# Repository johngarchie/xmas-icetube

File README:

##########################
## XMAS-ICETUBE PROJECT ##
##########################

Several years ago, my father gave me an Adafruit Ice Tube Clock kit as
a Christmas gift.  As an excuse to learn AVR programming, I started
playing with the firmware.  Eventually, none of the original Adafruit
code remained, and the result was a feature-rich reimplementation of
the Adafruit firmware.

Once the firmware was mature, I decided to revise the hardware design
to support many of the hacks and mods described on the Adafruit
forums.  With the help of other clock hackers, especially Phil DeGruy
and Russell Walker, the xmas-icetube hardware revision became a reality.

Today, the xmas-icetube firmware still runs on the Adafruit Ice Tube
Clock v1.1 as well as the xmas-icetube hardware revision.  For more
information on the firmware and hardware portions of this project,
please check out the firmware/README and hardware/README files.

Finally, although the xmas-icetube project is named after Christmas,
it is designed for use year-round.  The name is also a reference to
Christmas as a cultural holiday--not a religious one.  I sincerely
hope this project is compatible with all religions.

  John Archie <www.jarchie.com/email>
  April 2, 2014

###################
## USER FEEDBACK ##
###################

Below is a selection of comments posted on the Adafruit Clocks
forum.  They are listed in reverse chronological order.  And to
everyone quoted below:  Thank you all for the kind words!

  "[The xmas firmware] just worked from the beginning...
   Great documentation!"
     --MikeHg
       http://forums.adafruit.com/viewtopic.php?p=324261#p324261

  "Every mod works beautifully...  The code truly is clever...
   [John's] code is so clean that it's easy to add things."
     --rcb
       http://forums.adafruit.com/viewtopic.php?p=244224#p244224

  "This firmware is really cool. I highly recommend anyone with an
   ATmega328p lying around to program it with this firmware and use
   it instead of the one that comes with the kit."
     --motocoder
       http://forums.adafruit.com/viewtopic.php?p=243916#p243916

  "[John] has done a lot of nice work and added a lot of features.
   I can recommend his firmware as an upgrade..."
     --adafruit_support_bill,
       http://forums.adafruit.com/viewtopic.php?p=211476#p211476

  "...I LOVE your firmware, and for about 2 weeks I was still
   finding new options and features in the menu."
     --wildtang3nt
       http://forums.adafruit.com/viewtopic.php?p=204665#p204665

  "+10 for John's firmware!  Please do not let the 'xmas' name sway
   you from giving it a try. It's the most feature complete Ice-Tube
   Clock firmware to date."
     --revnull
       http://forums.adafruit.com/viewtopic.php?p=180609#p180609

##############
## FEATURES ##
##############

The xmas-icetube firmware offers the following improvements over
the official Adafruit firmware:

  - GPS synchronized timekeeping*
  - fully automatic compensation for clock drift
  - animated display transitions
  - multiple time and date formats
  - DST support (USA, EU, or manual)
  - pulsing display brightness during alarm and snooze
  - three alarm times for selectable days of the week
  - functional alarm during power outage**
  - finely adjustable alarm volume (from 0 to 10)
  - progressive alarm option (gradually increasing volume)
  - adjustable snooze duration
  - selectable alarm sound (high frequency beeps, low frequency beeps,
    high frequency three beep pulse, low frequency three beep pulse,
    Merry Christmas, Big Ben, Reveille, or For He's a Jolly Good Fellow)
  - 4-fold improvement in battery life
  - no beeping or time loss after external power failure
  - low battery warning before battery failure
  - per-digit brightness adjustment for uneven displays
  - larger range for user-configured display brightness
  - optionally disable display during specified time periods

*  An external GPS module, such as the Adafruit Ultimate GPS, is
   necessary to support GPS synchronized timekeeping.

** Without external power, the alarm sounds with loud high frequency
   beeps.  The only way to turn the alarm on or off is with the alarm
   switch.  Snooze is not supported.

The following additional features are supported on the xmas-icetube
hardware revision, but the Adafruit Ice Tube Clock v1.1 can be
modified to support any or all of the following as well:

  - automatic brightness control by ambient light
  - optionally disable display at night (when dark)
  - 25-fold improvement in battery life
  - highly accurate temperature compensated timekeeping
  - IV-18 tube driven to specifications (providing more even
    display illumination and preventing cathode poisoning)

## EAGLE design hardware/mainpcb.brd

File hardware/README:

####################################
## XMAS-ICETUBE HARDWARE REVISION ##
####################################

The xmas-icetube hardware revision is a revision of the Adafruit Ice Tube
Clock v1.1 hardware design to support many of the hacks and mods that have
been posted to the Adafruit forums over the years.  The original circuit
board has been extensively revised, but the case and overall look of the
clock is nearly identical to the original design.

The xmas-icetube hardware revision is discussed in the following thread:

    http://forums.adafruit.com/viewtopic.php?t=43836

##############
## FEATURES ##
##############

The xmas-icetube revision has the following improvements over the original
Adafruit design.  Although all of these features are incorporated into the
xmas-icetube board, many of the links given are oriented toward modifying
the original Adafruit clock to include the corresponding features.  Those
discussions are still relevant to the xmas-icetube revision, however.

* IV-18 tube driven to specifications:  The Adafruit design runs the IV-18
  in a way that results in inconsistent illumination across the display,
  and on some tubes, the effect is quite noticeable.  The original IV-18
  drive also accelerated the process of cathode poisoning.  Driving the
  IV-18 as the designers intended ensures uniform illumination and makes
  the tube less prone to cathode poisoning.

  http://forums.adafruit.com/viewtopic.php?t=23586
  http://forums.adafruit.com/viewtopic.php?t=41811

* Automatic dimming:  A photoresistor allows automatic dimming as
  appropriate for the ambient lighting.  The Adafruit design does,
  however, have an expansion area that can also be used to this end.

  http://forums.adafruit.com/viewtopic.php?t=12932

* 25-fold reduction in sleep current:  Unless the clock is without power
  for over a year, the battery should never need replacement.

  http://forums.adafruit.com/viewtopic.php?t=36697  
  http://forums.adafruit.com/viewtopic.php?p=219736#p219736

* Temperature compensated timekeeping:  A DS18B20 temperature sensor next
  to the clock crystal allows the software to compensate for temperature-
  related timekeeping error.  When combined with software-based drift
  correction, the resulting accuracy should be comparable to a temperature
  compensated quartz oscillator.

  http://forums.adafruit.com/viewtopic.php?t=43998
  http://forums.adafruit.com/viewtopic.php?f=41&t=12720

* GPS solder points:  Through-hole solder points allow easier installation
  of an external GPS unit for time synchronization.

  http://forums.adafruit.com/viewtopic.php?t=36873
  http://learn.adafruit.com/ice-tube-clock-kit/mods

  Alternatively, these solder points may also be used for installing a
  dedicated temperature compensated crystal oscillator instead of the
  DS18B20 temperature sensor above.

  http://forums.adafruit.com/viewtopic.php?&t=14941

* Robust in-system programming:  The clock may be programmed regardless of
  whether the display and side board are installed.  I recommend powering
  the clock with external power during programming, but a programming
  jumper provides a way to force the clock into sleep mode to ensure minimal
  power consumption if powered by the programmer instead.  I recommend
  using the jumper if using the AVR Dragon programmer, as the Dragon can
  barely provide enough power for programming alone.  But the jumper is
  unnecessary for most programmers including the Adafruit USBtinyISP.

  http://forums.adafruit.com/viewtopic.php?t=41975

* Robust microcontroller environment:  The microcontroller now has a
  decoupling capacitor and 10K pull-up on the reset pin.  These
  components make the clock less sensitive to electrical noise and
  ensure reliable operation.

Finally, although the xmas-icetube firmware is compatible with *both* the
original Adafruit clock and the xmas-icetube hardware revision, the
xmas-icetube revision is not compatible with firmwares developed
specifically for the Adafruit clock.

##########################
## COLLECTING THE PARTS ##
##########################

The current versions of the xmas-icetube custom parts are:

  - main board   (Rev. D)
  - side board   (Rev. C)
  - acrylic case (Rev. A)

I ordered my circuit boards from OSH Park and have shared those uploads
in case others would like to do the same:

    http://www.oshpark.com/shared_projects/6xAVpeHb
    http://www.oshpark.com/shared_projects/PiRXWH3F

I ordered the 3mm clear acrylic parts from Ponoko and have also shared
that design:

    http://www.ponoko.com/showroom/jarchie

For those in Europe, Formulor (http://www.formulor.de/) is an alternative
source for the acrylic parts.  Formulor is a Ponoko partner and accepts
the same SVG design format.  Many thanks to Tobias Scharmann for
suggesting this service.

See the enclosed bill of materials (BOM.csv) for a complete parts list,
including manufacturers, suppliers, and part numbers.

########################
## BUILDING THE CLOCK ##
########################

For aesthetic reasons, the xmas-icetube design uses TO-92 packages for the
voltage regulators, so their ability to burn off excess voltage is limited.
The 9VDC input should stay below 10v at 120 mA to be on the safe side:  A
standard regulated switching-type 9v adapter should work fine, but I
recommend against using an older, unregulated, transformer-type wall wort.

Alternatively, the board will accommodate regulators in TO-220 packages,
even though the silkscreen shows TO-92 packages.  The holes are a bit small
for TO-220s, so it might be necessary to file down the TO-220 leads to make
them narrower, but those packages will work with a bit of extra effort.
Although, I do prefer the TO-92s, TO-220s would look okay--just a bit bulky.

When assembling the parts, I suggest building the circuit incrementally and
testing each section after it is built.  See the Eagle schematics for the
parts in each section.

1.  Solder the "5V Power Supply" parts.  Connect the 9v adaptor and verify
    that the power supply outputs 5v; disconnect and proceed.

2.  Solder the "Temperature Sensor" parts.  (It's easier to solder R9
    before inserting the microcontroller into its socket.)

3.  Solder the "Microcontroller", "ISP Header", "Battery Sensor", and
    "Speaker" parts.  Program the ATmega328P (see the firmware/README file
    for details).  When powered with the AC adaptor, the speaker should
    beep when powered for the first time.  Keep the AC adaptor connected
    for at least ten seconds after hearing the beep.

    If the speaker does not beep, ensure the programming jumper has been
    removed and that the ATmega328P is properly programmed.  If the speaker
    beeps repeatedly at 8 second intervals, the problem is most likely with
    the crystal oscillator.  If the oscillator parts and connections are
    good, cleaning excess rosin from the board with a toothbrush and
    rubbing alcohol might fix the problem, but make sure the board is
    completely dry before powering it again.

4.  Solder the "5VAC Cathode/Filament Supply" parts.  Measure the AC voltage
    between the two push-pull outputs (AC1 and AC2).  The push-pulls should
    provide high frequency, square wave, alternating current, which most
    multimeters cannot measure accurately.  Without a load, the LM317 will not
    effectively regulate voltage anyway, so multimeter accuracy does not
    matter.  So ensure that AC1 and AC2 are providing alternating current,
    but the amount of voltage measured is not important.

5.  Solder the "Tube 30-60VDC Boost Supply" parts.  Note that the joined
    leads of Q2 should be oriented toward C6.  Connect the 9v adaptor and
    verify that the boost circuit indeed provides 50-60 volts.

6.  Solder the "VFD Anode/Segment Controller" and "VFD Tube / Side PCB"
    parts.  Attach the side board to the main board, connect the 9v
    adaptor, and verify that the VFD display is functional.

7.  Solder the "Buttons and Alarm Switch" parts.  Connect the 9v adaptor
    and verify that the buttons and alarm switch function properly.

8.  Solder the "Battery Backup" parts and insert a battery, but before
    soldiering the battery case, apply a small amount of solder to the
    battery's ground connection (large square pad).  A small amount of
    solder will add height to the square pad connection and ensure a good
    connection between the battery and ground.

    Connect the 9v adaptor, set the time, disconnect the 9v adaptor for ten
    minutes, connect it again, and verify that the clock kept the correct
    time.  Because the clock is extremely power-efficient during sleep, the
    capacitors store enough charge to keep the clock running for 3-5
    minutes.  Leaving the clock unplugged for ten minutes ensures that the
    backup battery is actually in use.

9.  Solder the "Light Sensor" parts.  So the clock can accurately gauge
    ambient lighting, install the photoresistor such that it points towards
    the front of the clock and away from the tube.  Connect the 9v adaptor,
    and using a flashlight, lamp, or similar, verify that the clock
    responds to changes in ambient light.

10. Assemble the acrylic case and enjoy!

##############################
## EDITING THE DESIGN FILES ##
##############################

The board revisions can be opened and and modified with Eagle,
which is available from CadSoft:

    http://www.cadsoftusa.com/

The case revision may be viewed and modified in Inkscape:

    http://inkscape.org/

######################
## ACKNOWLEDGEMENTS ##
######################

The Adafruit Ice Tube Clock board was loosely based on the inGrid
IV-18 clock by Riad S. Wahby.  My xmas-icetube board revision is based
on the Adafruit Ice Tube Clock board by Lady Ada.

The clock case was originally designed by Amanda Wozniak (w0z), and I have
only made minor adjustments to her design.  Adafruit forum user Daygecko
also deserves credit for finding clear machine nuts and bolts from
McMaster-Carr, which give the assembled case a cleaner look.

Phil DeGruy (PhilD13) reviewed my initial design and suggested several
components; the ZVN2110A and ZVP2001A MOSFETs in particular were
especially useful for generating AC for the IV-18 filament.  Phil
also found many alternative parts for the bill of materials which cost
less than my original selections.

I also had fruitful discussions with both Phil DeGruy and Russell Walker
(Russell27), mostly  in regard to properly driving the IV-18 tube.  Phil
and Russell built their own xmas-icetube clocks and provided useful
feedback on the overall design.

Because I am inexperienced in electronics design, I must add the following
disclaimer:  Those cited in this section cannot be faulted for any bugs in
the xmas-icetube hardware revision.

#############
## LICENSE ##
#############

The xmas-icetube hardware revision may be used under the Attribution-
ShareAlike 3.0 (CC BY-SA 3.0), available from Creative Commons:

    http://creativecommons.org/licenses/by-sa/3.0/

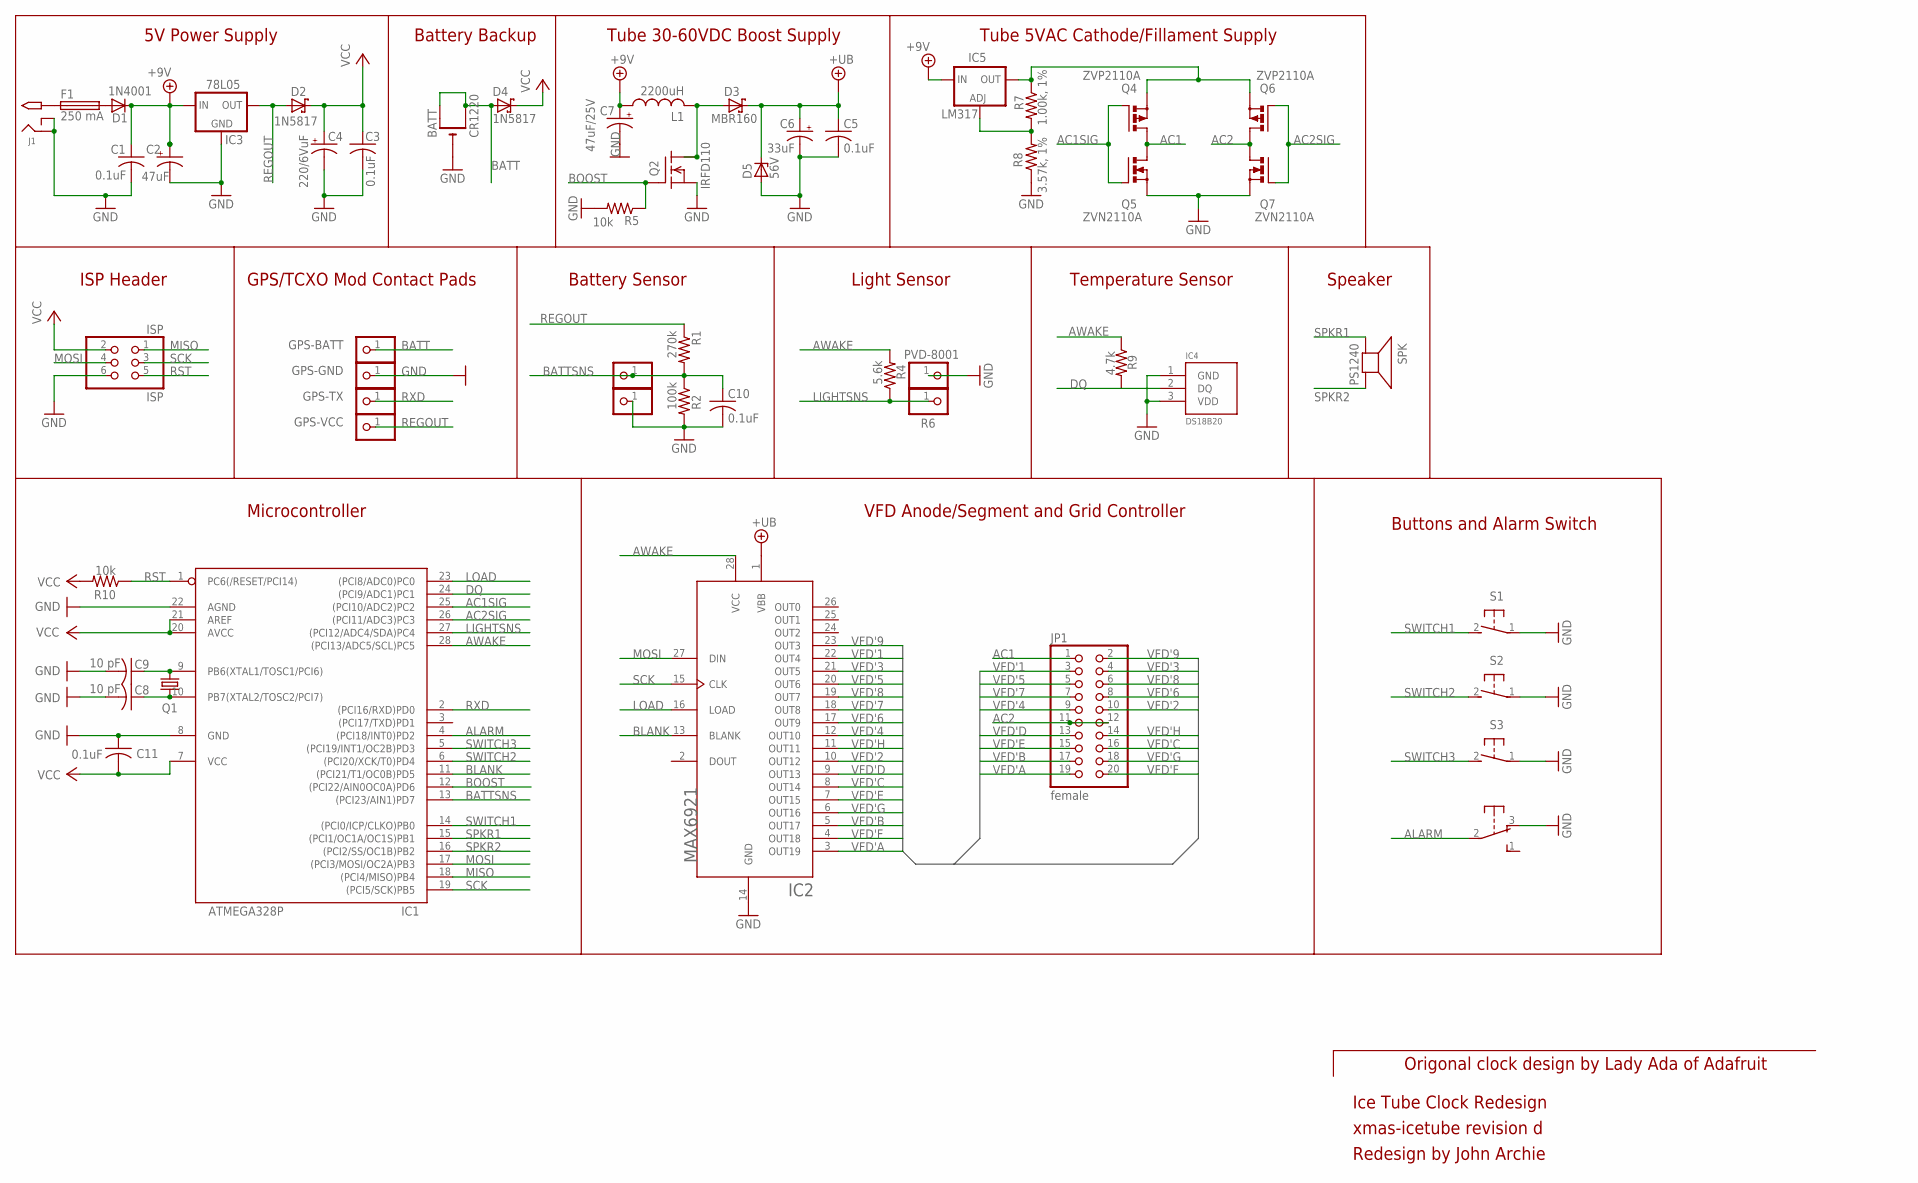
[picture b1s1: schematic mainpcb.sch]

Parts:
BATT: CR1220; CR1220-THM
C1, C3, C11: 0.1uF; C025-025X050
C2: 47uF; E2,5-6
C4: 220/6VuF; E2,5-6
C5, C10: 0.1uF; C025-024X044
C6: 33uF; E3,5-8
C7: 47uF/25V; E2,5-6
C8, C9: 10 pF; C025-024X044
CT2, CT3: PINHD-1X1; 1X01
D1: 1N4001; DO41-10
D2, D4: 1N5817; DO41-10
D3: MBR160; DO41-10
D5: 56V; DO41Z10
F1: 250 mA; TE5
GPS-BATT: PINHD-1X1; 1X01
GPS-GND: PINHD-1X1; 1X01
GPS-TX: PINHD-1X1; 1X01
GPS-VCC: PINHD-1X1; 1X01
IC1: ATMEGA328P; DIL28/3
IC2: MAX6921; PLCC-S28
IC3: 78L05; TO92-LINE
IC4: DS18B20; TO92
IC5: LM317; TO92-LINE
ISP: ISP; 2X03
J1: 2.1MMJACK; PJ-102A
JP1: female; 2X10
L1: 2200uH; 6000
Q1: 32.768 khz; TC26V
Q2: IRFD110; DIL04
Q4, Q6: ZVP2110A; TO92-FLAT
Q5, Q7: ZVN2110A; TO92-FLAT
R1: 270k; 0207/10
R2: 100k; 0207/10
R4: 5.6k; 0207/5V
R5, R10: 10k; 0207/5V
R6: PVD-8001; 1X01
R6.1: PINHD-1X1; 1X01
R7: 1.00k, 1%; 0207/5V
R8: 3.57k, 1%; 0207/5V
R9: 4.7k; 0207/10
S1, S2, S3: 31-XX; B3F-31XX
SPK: PS1240; PS12
SW1: OS102011MA1Q

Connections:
+9V: C1.1, C2.+, C7.+, D1.C, IC3.3 (IN), IC5.3 (IN), L1.1
+UB: C5.1, C6.+, D3.C, D5.C, IC2.1 (VBB)
AC1: JP1.1, Q4.3 (D), Q5.3 (D)
AC1SIG: IC1.25 ((PCI10/ADC2)PC2), Q4.2 (G), Q5.2 (G)
AC2: JP1.11, JP1.12, Q6.3 (D), Q7.3 (D)
AC2SIG: IC1.26 ((PCI11/ADC3)PC3), Q6.2 (G), Q7.2 (G)
ALARM: IC1.4 ((PCI18/INT0)PD2), SW1.2
AWAKE: IC1.28 ((PCI13/ADC5/SCL)PC5), IC2.28 (VCC), R4.2, R9.1
BATT: BATT.+1 (+), BATT.+2 (+1), D4.A, GPS-BATT.1
BATTSNS: C10.1, CT2.1, IC1.13 ((PCI23/AIN1)PD7), R1.2, R2.1
BLANK: IC1.11 ((PCI21/T1/OC0B)PD5), IC2.13 (BLANK)
BOOST: IC1.12 ((PCI22/AIN0OC0A)PD6), Q2.3 (G), R5.1
DQ: IC1.24 ((PCI9/ADC1)PC1), IC4.2 (DQ), R9.2
GND: BATT.-, C1.2, C2.-, C3.2, C4.-, C5.2, C6.-, C7.-, C8.2, C9.2, C10.2, C11.1, CT3.1, D5.A, GPS-GND.1, IC1.8 (GND), IC1.22 (AGND), IC2.14 (GND), IC3.2 (GND), IC4.1 (GND), IC4.3 (VDD), ISP.6, J1.RING, J1.RING_SW, Q2.4 (S), Q5.1 (S), Q7.1 (S), R2.2, R5.2, R6.1, R8.1, S1.1, S2.1, S3.1, SW1.3 (O)
LIGHTSNS: IC1.27 ((PCI12/ADC4/SDA)PC4), R4.1, R6.1.1
LOAD: IC1.23 ((PCI8/ADC0)PC0), IC2.16 (LOAD)
MISO: IC1.18 ((PCI4/MISO)PB4), ISP.1
MOSI: IC1.17 ((PCI3/MOSI/OC2A)PB3), IC2.27 (DIN), ISP.4
unnamed: C9.1, IC1.9 (PB6(XTAL1/TOSC1/PCI6)), Q1.2
unnamed: D3.A, L1.2, Q2.1 (D), Q2.2 (D1)
unnamed: C8.1, IC1.10 (PB7(XTAL2/TOSC2/PCI7)), Q1.1
unnamed: F1.1, J1.TIP
unnamed: D1.A, F1.2
unnamed: IC5.1 (ADJ), R7.2, R8.2
unnamed: IC5.2 (OUT), Q4.1 (S), Q6.1 (S), R7.1
REGOUT: D2.A, GPS-VCC.1, IC3.1 (OUT), R1.1
RST: IC1.1 (PC6(/RESET/PCI14)), ISP.5, R10.1
RXD: GPS-TX.1, IC1.2 ((PCI16/RXD)PD0)
SCK: IC1.19 ((PCI5/SCK)PB5), IC2.15 (CLK), ISP.3
SPKR1: IC1.15 ((PCI1/OC1A/OC1S)PB1), SPK.P$1 (+)
SPKR2: IC1.16 ((PCI2/SS/OC1B)PB2), SPK.P$2 (-)
SWITCH1: IC1.14 ((PCI0/ICP/CLKO)PB0), S1.2 (S)
SWITCH2: IC1.6 ((PCI20/XCK/T0)PD4), S2.2 (S)
SWITCH3: IC1.5 ((PCI19/INT1/OC2B)PD3), S3.2 (S)
VCC: C3.1, C4.+, C11.2, D2.C, D4.C, IC1.7 (VCC), IC1.20 (AVCC), IC1.21 (AREF), ISP.2, R10.2
VFD'1: IC2.22 (OUT4), JP1.3
VFD'2: IC2.10 (OUT12), JP1.10
VFD'3: IC2.21 (OUT5), JP1.4
VFD'4: IC2.12 (OUT10), JP1.9
VFD'5: IC2.20 (OUT6), JP1.5
VFD'6: IC2.17 (OUT9), JP1.8
VFD'7: IC2.18 (OUT8), JP1.7
VFD'8: IC2.19 (OUT7), JP1.6
VFD'9: IC2.23 (OUT3), JP1.2
VFD'A: IC2.3 (OUT19), JP1.19
VFD'B: IC2.5 (OUT17), JP1.17
VFD'C: IC2.8 (OUT14), JP1.16
VFD'D: IC2.9 (OUT13), JP1.13
VFD'E: IC2.7 (OUT15), JP1.15
VFD'F: IC2.4 (OUT18), JP1.20
VFD'G: IC2.6 (OUT16), JP1.18
VFD'H: IC2.11 (OUT11), JP1.14

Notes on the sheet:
5V Power Supply
GPS/TCXO Mod Contact Pads
Tube 30-60VDC Boost Supply
Ice Tube Clock Redesign
xmas-icetube revision d
Redesign by John Archie
Tube 5VAC Cathode/Fillament Supply
ISP Header
Battery Backup
Microcontroller
VFD Anode/Segment and Grid Controller
Buttons and Alarm Switch
Battery Sensor
Light Sensor
Temperature Sensor
Speaker
Origonal clock design by Lady Ada of Adafruit

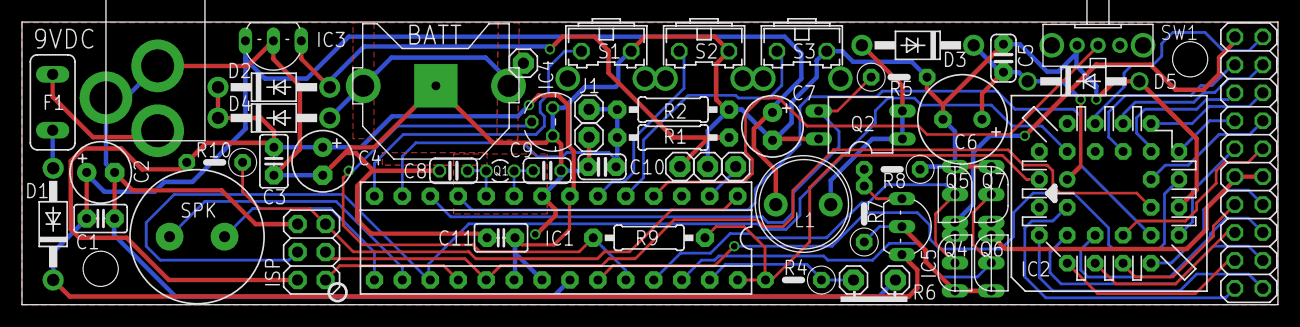
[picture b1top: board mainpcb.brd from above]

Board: 2 copper layers, 114.2 x 25.7 mm, 54 parts (0 on the bottom side), 52 nets.

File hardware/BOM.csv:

"Name","Description","Manufacturer","Manufacturer Part","Supplier","Supplier Part"
"main board","xmas-icetube main board (rev. d)","OSH Park",,"OSH Park",
"side board","xmas-icetube side board (rev. c) ","OSH Park",,"OSH Park",
"acrylic case","xmas-icetube acrylic case (rev. a)","Ponoko",,"Ponoko",
"nuts (10x)","4-40 polycarbonate hex nut","McMaster-Carr","94905A005","McMaster-Carr","94905A005"
"bolts (8x)","4-40 polycarbonate phillips screw","McMaster-Carr","93140A109","McMaster-Carr","93140A109"
"9VAC","9 v adaptor, 2.1mm jack (International)","CUI Inc","EMSA090067-P5P-SZ","Digi-Key","T1085-P5P-ND"
"9VAC (alt)","9 volt adaptor, 2.1mm jack (North America)","Volgen America/Kaga Electronics USA","KTPS05-09006U","Digi-Key","62-1167-ND"
"BATT","coin cell","Energizer","CR1220","Amazon","B003CU3E2Q"
"display","antique vacuum florescent display ","Russia (discontinued, NOS)","IV-18","eBay/Adafruit","IV-18"
"9VAC'","2.1mm power jack","CUI Inc","PJ-202A","Digi-Key","CP-202A-ND"
"BATT'","coin cell holder","Keystone Electronics",3001,"Digi-Key","3001K-ND"
"C1,C3,C10,C11","0.1uF 50v cap","TDK Corporation","FK18X7R1H104K","Digi-Key","445-5303-ND"
"C2,C7","47uF 35v cap","Panasonic Electronic Components","ECA-1VHG470","Digi-Key","P5550-ND"
"C4","220uF 6.3v cap","Panasonic Electronic Components","ECA-0JHG221","Digi-Key","P5506-ND"
"C5","0.1uF 100v cap","AVX Corporation","SR201C104KAR","Digi-Key","478-4855-ND"
"C6","33uF 100v cap","Panasonic Electronic Components","EEU-FC2A330L","Digi-Key","P10772-ND"
"C8,C9","10pF 50v cap","Vishay BC Components","K100J15C0GF5TL2","Digi-Key","BC1001CT-ND"
"D1","50v 1A general purpose diode","Fairchild Semiconductor","1N4001","Digi-Key","1N4001FSCT-ND"
"D2,D4","20v 1A Schottky diode","Fairchild Semiconductor","1N5817","Digi-Key","1N5817FSCT-ND"
"D3","60v 1A Schottky diode","ON Semiconductor","MBR160G","Digi-Key","MBR160GOS-ND"
"D5","56v 1.3W Zener diode","Vishay Semiconductor Diodes Division","1N4758A-TR","Digi-Key","1N4758AVSCT-ND"
"F1","250 mA resettable fuse","TE Connectivity","RXEF025-2","Digi-Key","RXEF025CT-ND"
"IC1","Microcontroller","Atmel","ATMEGA328P-PU","Digi-Key","ATMEGA328P-PU-ND "
"IC1'","28 pin DIP socket","3M","4828-3004-CP","Digi-Key","3M5480-ND"
"IC2","VFD grid/segment driver","Maxim Integrated","MAX6921AQI+","Digi-Key","MAX6921AQI+-ND"
"IC2'","28 pin PLCC socket","Assmann WSW Components","A-CCS28-Z-R","Digi-Key","AE10055-ND"
"IC3","5v voltage regulator","ON Semiconductor","MC78L05ABPG","Digi-Key","MC78L05ABPGOS-ND"
"IC4","temperature sensor","Maxim Integrated","DS18B20+","Mouser","700-DS18B20+"
"IC5","LM317 voltage regulator","ON Semiconductor","LM317LZG","Digi-Key","LM317LZGOS-ND"
"ISP","2x3 0.1inx0.1in ISP header","3M","961206-6404-AR","Digi-Key","3M9459-ND"
"J1","standard jumper","Sullins Connector Solutions","QPC02SXGN-RC","Digi-Key","S9337-ND"
"J1 (alt)","jumper with handle (alternative)","Sullins Connector Solutions","NPC02SXON-RC","Digi-Key","S9341-ND"
"J1'","1x2 0.1in male header","FCI","77311-118-02LF","Digi-Key","609-4434-ND"
"JP1","2x10 0.1inx0x.1in female header","Sullins Connector Solutions","PPPC102LFBN-RC","Digi-Key","S6106-ND"
"JP2","2x10 0.1inx0x.1in male right angle header","FCI","68021-120HLF","Digi-Key","609-3338-ND"
"L1","2.2mH 0.24A inductor","Murata Power Solutions Inc","13R225C","Digi-Key","811-2054-ND"
"Q1","clock crystal oscillator","ABRACON","AB38T-32.768KHZ","Mouser","815-AB38T-32.768KHZ"
"Q2","100v N-channel MOSFET","Vishay Siliconix","IRFD110PBF","Digi-Key","IRFD110PBF-ND"
"Q3","removed from design",,,,
"Q4,Q6","100v P-channel MOSFET","Diodes Inc","ZVP2110A","Digi-Key","ZVP2110A-ND"
"Q5,Q7","100v N-channel MOSFET","Diodes Inc","ZVN2110A","Digi-Key","ZVN2110A-ND"
"R1","270k 5% resistor","Yageo","CFR-25JB-52-270K","Digi-Key","270KQBK-ND"
"R2","100k 5% resistor","Yageo","CFR-25JB-52-100K","Digi-Key","100KQBK-ND"
"R3","removed from design",,,,
"R4","5.6k 5% resistor","Yageo","CFR-25JB-52-5K6","Digi-Key","5.6KQBK-ND"
"R5,R10","10k 5% resistor","Yageo","CFR-25JB-52-10K","Digi-Key","10KQBK-ND"
"R6","photoresistor","Advanced Photonix Inc","PDV-P8001","Digi-Key","PDV-P8001-ND"
"R7","1.00k 1% resistor","Yageo","MFR-25FBF52-1K","Digi-Key","1.00KXBK-ND"
"R8","3.57k 1% resistor","Yageo","MFR-25FBF52-3K57","Digi-Key","3.57KXBK-ND"
"R9","4.7k 5% resistor","Yageo","CFR-25JB-52-4K7","Digi-Key","4.7KQBK-ND "
"S1,S2,S3","right angle tactile switch","Panasonic Electronic Components","EVQ-PF008K","Digi-Key","P10880S-ND"
"SPK","piezo speaker","TDK","PS1240P02BT","Mouser","810-PS1240P02BT"
"SW1","right angle SPDT switch","C&K Components","0S102011MA1QN1","Mouser","611-OS102011MA1QN1"

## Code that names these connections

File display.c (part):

// display.c  --  low-level control of VFD display
// (Display contents are controlled in mode.c)
//
//    PB5 (SCK)                      MAX6921 CLK pin
//    PB3 (MOSI)                     MAX6921 DIN pin
//    PC5*                           photoresistor pull-up
//    PC4 (ADC4)                     photoresistor voltage
//    PC3**                          MAX6921 BLANK pin
//    PC3***			     alternating current signal pin
//    PC2***			     alternating current signal pin
//    PC0                            MAX6921 LOAD pin
//    PD6                            boost transistor
//    PD3*                           vfd power transistor
//    counter/timer0                 boost (PD6) and semiticks
//    analog to digital converter    photoresistor (ADC4) voltage
//
//   * PC5 is used to directly power the photoresistor, vfd power, and
//     temperature sensor pull-up if configured for the xmas-icetube
//     hardware design.
//
//  ** PD5--not PC3--is used to control the BLANK pin if and only if
//     the IV-18 to-spec hack is enabled.
//
// *** PC3 and PC2 are used to generate an alternating current signal
//     to power the IV-18 filament if and only if the IV-18 to-spec 
//     hack is enabled.
//
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
    // disable boost and vfd
#ifndef XMAS_DESIGN
    DDRD  |= _BV(PD3); // enable boost fet and vfd transistor
    PORTD |= _BV(PD3); // MAX6921 power off (push high)
#endif  // !XMAS_DESIGN
    DDRD  |=  _BV(PD6); // enable boost fet and vfd transistor
    PORTD &= ~_BV(PD6); // boost fet off (pull low)

#ifdef VFD_TO_SPEC
    // configure MAX6921 load and blank pins
    DDRC  |=  _BV(PC0); // set blank pin to output
    PORTC &= ~_BV(PC0); // clamp blank pin to ground
    DDRD  |=  _BV(PD5); // set load pin to output
    PORTD &= ~_BV(PD5); // clamp load pin to ground
#else
    // configure MAX6921 load and blank pins
    DDRC  |=  _BV(PC0) |  _BV(PC3); // set to output
    PORTC &= ~_BV(PC0) & ~_BV(PC3); // clamp to ground
#endif  // VFD_TO_SPEC

    // configure spi sck and mosi pins as floating inputs
    // (these pins seem to use less power when configured
    // as inputs *without* pull-ups!?!?)
    DDRB  &= ~_BV(PB5) & ~_BV(PB3);  // set to input

    // configure photoresistor pull-up pin
    DDRC  |=  _BV(PC5);  // set pin as output
    PORTC &= ~_BV(PC5);  // pull to ground

    // disable digital circuitry on photoresistor pins
    DIDR0 |= _BV(ADC5D) | _BV(ADC4D);
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
#ifdef VFD_TO_SPEC
    // configure AC signal pins
    DDRC  |=  _BV(PC2) |  _BV(PC3);  // set as output
    PORTC &= ~_BV(PC2) & ~_BV(PC3);  // pull to ground
#endif  // VFD_TO_SPEC
}

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void display_wake(void) {
    // enable external and internal photoresistor pull-ups (the latter
    // ensures a defined value if no photoresistor installed)
    PORTC |= _BV(PC5) | _BV(PC4);  // output +5v, enable pull-up

    // enable analog to digital converter
    power_adc_enable();
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    ADCSRA = _BV(ADEN) | _BV(ADSC) | _BV(ADPS2) | _BV(ADPS1);

    // configure spi sck and mosi pins as outputs
    DDRB |= _BV(PB5) | _BV(PB3);


#ifdef VFD_TO_SPEC
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
    // MAX6921 power on (pull low)
#ifndef XMAS_DESIGN
    PORTD &= ~_BV(PD3);
#endif  // !XMAS_DESIGN

#ifdef VFD_TO_SPEC
    // power VFD cathode (heater)
    PORTC |=  _BV(PC2);
    PORTC &= ~_BV(PC3);
#endif  // VFD_TO_SPEC

    display.off_timer = DISPLAY_OFF_TIMEOUT;
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    // disable Timer/Counter0
    TCCR0A = TCCR0B = 0;

    PORTD &= ~_BV(PD6); // boost fet off (pull low)
#ifndef XMAS_DESIGN
    PORTD |=  _BV(PD3); // MAX6921 power off (pull high)
#endif  // !XMAS_DESIGN

    // disable external and internal photoresistor pull-ups
    PORTC &= ~_BV(PC5) & ~_BV(PC4);  // pull to ground, disable pull-up

    // disable analog to digital converter
    ADCSRA = 0;  // disable ADC before power_adc_disable()
    power_adc_disable();

#ifdef VFD_TO_SPEC
    // configure MAX6921 LOAD and BLANK pins
    PORTC &= ~_BV(PC0); // clamp to ground
    PORTD &= ~_BV(PD5); // clamp to ground
#else
    // configure MAX6921 LOAD and BLANK pins
    PORTC &= ~_BV(PC0) & ~_BV(PC3); // clamp to ground
#endif  // VFD_TO_SPEC

    // configure MAX6921 CLK and DIN pins
    // (these pins seem to use less power when configured
    // as inputs *without* pull-ups!?!?)
    DDRB  &= ~_BV(PB5) & ~_BV(PB3);  // set as input
    PORTB &= ~_BV(PB5) & ~_BV(PB3);  // disable pull-ups

#ifdef VFD_TO_SPEC
    // disable VFD cathode (heater fillament)
    PORTC &= ~_BV(PC2) & ~_BV(PC3);  // pull to ground
#endif  // VFD_TO_SPEC
}

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		&& !(display.status & DISPLAY_DISABLED)) {
	    display.status |=  DISPLAY_DISABLED;
	    TCCR0A = _BV(WGM00) | _BV(WGM01);
	    PORTD &= ~_BV(PD6);  // boost fet off (pull low)
#ifndef XMAS_DESIGN
	    PORTD |=  _BV(PD3);  // MAX6921 power off (pull high)
#endif  // !XMAS_DESIGN
#ifdef VFD_TO_SPEC
	    // disable VFD cathode (heater fillament)
	    PORTC &= ~_BV(PC2) & ~_BV(PC3);  // pull to ground
#endif  // VFD_TO_SPEC
	}
    }
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		     | _BV(WGM00) | _BV(WGM01);

	    // power VFD cathode (heater fillament)
	    PORTC |=  _BV(PC2);
	    PORTC &= ~_BV(PC3);
#else
	    TCCR0A = _BV(COM0A1) | _BV(WGM00) | _BV(WGM01);
#endif  // VFD_TO_SPEC
#ifndef XMAS_DESIGN
	    PORTD &= ~_BV(PD3);  // MAX6921 power on (pull low)
#endif  // !XMAS_DESIGN
	}
    }
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
	// blank display to prevent ghosting
#ifdef VFD_TO_SPEC
	// disable pwm on blank pin
	TCCR0A = _BV(COM0A1) | _BV(WGM00) | _BV(WGM01);
	PORTD |= _BV(PD5);  // push MAX6921 BLANK pin high
#else
	PORTC |= _BV(PC3);  // push MAX6921 BLANK pin high
#endif  // VFD_TO_SPEC
    }

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        for(; bitflag; bitflag >>= 1) {
            if(bitbyte & bitflag) {
                // output high on MAX6921 DIN pin
                PORTB |= _BV(PB3);
            } else {
                // output low on MAX6921 DIN pin
                PORTB &= ~_BV(PB3);
            }

            // pulse MAX6921 CLK pin:  shifts DIN input into
            // the 20-bit shift register on rising edge
            PORTB |=  _BV(PB5);
            PORTB &= ~_BV(PB5);
        }

	bitflag = 0x80;
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    
    // pulse MAX6921 LOAD pin:  transfers shift
    // register to latch when high; latches when low
    PORTC |=  _BV(PC0);
    PORTC &= ~_BV(PC0);

    if(!(display.status & DISPLAY_DISABLED)) {
	// unblank display to prevent ghosting
#ifdef VFD_TO_SPEC
	// enable pwm on blank pin
	TCCR0A = _BV(COM0A1) | _BV(COM0B0) | _BV(COM0B1) |
	         _BV(WGM00)  | _BV(WGM01);
	TCNT0  = 0xFF;  // set counter to max
#else
	PORTC &= ~_BV(PC3);  // pull MAX6921 BLANK pin low
#endif  // VFD_TO_SPEC
    }

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
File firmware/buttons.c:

// buttons.c  --  button press detection
// (button presses are processed in mode.c)
//
// Note that PD5 is the default menu button pin, but PC4 is used
// instead when the anode-cathode to-spec hack is enabled.
// 
//    PD5*   menu button
//    PD4    plus button
//    PB0    set button
//
// * PB4--not PD5--is used to control the BLANK pin if and only if
//   the IV-18 to-spec hack is enabled.
//


#include <avr/io.h>  // for using avr register names


#include "buttons.h"
#include "piezo.h"  // for clicking on button presses
#include "usart.h"  // for debugging output


#ifdef XMAS_DESIGN
// menu button bit and registers
#define MENU_BIT  PB0
#define MENU_PORT PORTB
#define MENU_DDR  DDRB
#define MENU_PIN  PINB

// set button bit and registers
#define SET_BIT  PD4
#define SET_PORT PORTD
#define SET_DDR  DDRD
#define SET_PIN  PIND

// plus button bit and registers
#define PLUS_BIT  PD3
#define PLUS_PORT PORTD
#define PLUS_DDR  DDRD
#define PLUS_PIN  PIND

#else

// menu button bit and registers
#ifdef VFD_TO_SPEC
#define MENU_BIT  PB4
#define MENU_PORT PORTB
#define MENU_DDR  DDRB
#define MENU_PIN  PINB
#else
#define MENU_BIT  PD5
#define MENU_PORT PORTD
#define MENU_DDR  DDRD
#define MENU_PIN  PIND
#endif  // VFD_TO_SPEC

// set button bit and registers
#define SET_BIT  PB0
#define SET_PORT PORTB
#define SET_DDR  DDRB
#define SET_PIN  PINB

// plus button bit and registers
#define PLUS_BIT  PD4
#define PLUS_PORT PORTD
#define PLUS_DDR  DDRD
#define PLUS_PIN  PIND

#endif  // XMAS_DESIGN


// extern'ed button input data
volatile buttons_t buttons;


// set initial state after system reset
void buttons_init(void) {
    buttons.state = buttons.pressed = 0;
    buttons_sleep(); // clamp button pins to ground
}


// clamp button pins to ground
void buttons_sleep(void) {
    // disable pull-up resistors
    MENU_PORT &= ~_BV(MENU_BIT);
    SET_PORT  &= ~_BV(SET_BIT);
    PLUS_PORT &= ~_BV(PLUS_BIT);

    // set to output (clamp to ground)
    MENU_DDR |= _BV(MENU_BIT);
    SET_DDR  |= _BV(SET_BIT);
    PLUS_DDR |= _BV(PLUS_BIT);
}


// enable button pins as inputs with pull-ups enabled
void buttons_wake(void) {
    // set to input
    MENU_DDR &= ~_BV(MENU_BIT);
    SET_DDR  &= ~_BV(SET_BIT);
    PLUS_DDR &= ~_BV(PLUS_BIT);

    // enable pull-up resistors
    MENU_PORT |= _BV(MENU_BIT);
    SET_PORT  |= _BV(SET_BIT);
    PLUS_PORT |= _BV(PLUS_BIT);
}


// check for button presses every semisecond
void buttons_semitick(void) {
    uint8_t sensed = 0;  // which buttons are pressed?

    // check the menu button (button one)
    if(!(MENU_PIN & _BV(MENU_BIT))) sensed |= BUTTONS_MENU;

    // check the plus button (button three)
    if(!(PLUS_PIN & _BV(PLUS_BIT))) sensed |= BUTTONS_PLUS;

    // check the set button (button two)
    if(!(SET_PIN & _BV(SET_BIT))) sensed |= BUTTONS_SET;

    // timers for button debouncing and repeating
    static uint8_t debounce_timer = 0;
    static uint16_t pressed_timer = 0;

    // debounce before storing the currently pressed buttons
    if(buttons.pressed != sensed && (buttons.state & 0x0F) == sensed) {
	if(++debounce_timer >= BUTTONS_DEBOUNCE_TIME) {
	    buttons.pressed = sensed;
	    buttons.state &= 0x0F;  // clear process and repeating flags
	    pressed_timer = 0;
	}
    } else {
	buttons.state &= 0xF0;   // clear button flags
	buttons.state |= sensed; // set new button flags
	debounce_timer = 0;
    }

    // if any buttons are pressed, periodically clear processed flag
    // to allow for press-and-hold repeating
    if(buttons.pressed) {
	++pressed_timer;

	if(buttons.state & BUTTONS_REPEATING) {
	    if(pressed_timer >= BUTTONS_REPEAT_RATE) {
		buttons.state &= ~BUTTONS_PROCESSED;
		pressed_timer = 0;
	    }
	} else {
	    if(pressed_timer >= BUTTONS_REPEAT_AFTER) {
		buttons.state |= BUTTONS_REPEATING;
	    }
	}
    }
}


// process a button press: if a button is pressed and not
// previously processed, return it.  otherwise return zero.
uint8_t buttons_process(void) {
    // return nothing if there is no button pressed
    // or if any buttons pressed have already been processed
    if(buttons.state & BUTTONS_PROCESSED || !buttons.pressed) return 0;

    // mark this button press as processed
    buttons.state |= BUTTONS_PROCESSED;

    // make a nice, satisfying click with processed button press
    piezo_click();

    // return the pressed buttons
    return buttons.pressed;
}

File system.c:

// system.c  --  system functions (idle, sleep, interrupts)
//
//    PB4 (MISO)           unused pin (unless anode-grid to-spec hack)
//    PC2                  unused pin
//    PC1                  power from voltage regulator or unused pin
//    AIN1 (PD7)           divided system voltage
//    analog comparator    detects low voltage (AIN1)
//
// system_init() disables all modules in PRR register: TWI, timer2, timer1,
// timer0, SPI, USART, and ADC.  These modules are and disabled as-needed in
// the various *_wake() functions in other *.c files.
//


#include <avr/interrupt.h> // for enabling and disabling interrupts
#include <avr/power.h>     // for disabling microcontroller modules
#include <avr/sleep.h>     // for entering low-power modes
#include <avr/wdt.h>       // for using the watchdog timer
#include <util/atomic.h>   // for non-interruptable blocks
#include <util/delay.h>    // for enabling delays


#include "system.h"
#include "usart.h"  // for debugging output


// extern'ed system status data
volatile system_t system;


// enable low-power detection and disables microcontroller modules
void system_init(void) {
    system.initial_mcusr = MCUSR;  // save MCUSR
    MCUSR = 0;  // clear any watchdog timer flags
    wdt_enable(WDTO_8S);  // enable eight-second watchdog timer

    system.status &= ~SYSTEM_SLEEP;

    // enable pull-up resistors on unused pins to ensure a defined value
#ifndef VFD_ANODE_GRID_TO_SPEC
    PORTB |= _BV(PB4);
#endif  // ~VFD_ANODE_GRID_TO_SPEC
    // leave PC1 tri-stated in case clock is wired
    // for the depricated exteneded battery hack
#ifndef VFD_CATHODE_TO_SPEC
    PORTC |= _BV(PC2);
#endif  // ~VFD_CATHODE_TO_SPEC

    // use internal bandgap as reference for analog comparator
    // and enable analog comparator interrupt on falling edge
    // of AIN1 (interrupt triggers when adaptor power fails)
    ACSR = _BV(ACBG) | _BV(ACIE) | _BV(ACI);

    // disable digital input on analog comparator input, AIN1
    DIDR1 = _BV(AIN1D);

    // disable all features for power savings; individual features are enabled
    // one-by-one in appropriate submodules
    power_all_disable();
}


// repeatedly enter idle mode forevermore
void system_idle_loop(void) {
    sleep_enable();
    for(;;) {
	cli();
	set_sleep_mode(SLEEP_MODE_IDLE);
	sei();
	sleep_cpu();
    }
}


// repeatedly enter power save mode until power restored
void system_sleep_loop(void) {
    sleep_enable();                 // permit sleep mode
    system.status |= SYSTEM_SLEEP;  // set sleep flag
    wdt_disable();                  // disable watchdog
    ACSR = _BV(ACD) | _BV(ACI);     // disable analog comparator and
    				    // clear analog comparator interrupt
    do {
	do {
	    // disable analog comparator to save power; analog comparator
	    // will be enabled in system_tick() or system_wake()
	    ACSR = _BV(ACD);

	    // wait until asynchronous updates are complete
	    // or system might fail to wake from sleep
	    while(ASSR & (  _BV(TCN2UB) 
			  | _BV(OCR2AUB) | _BV(OCR2BUB)
			  | _BV(TCR2AUB) | _BV(TCR2BUB) ));

	    if(system.status & SYSTEM_ALARM_SOUNDING) {
		// if the alarm buzzer is active, remain in idle mode
		// so buzzer continues sounding for next second
		set_sleep_mode(SLEEP_MODE_IDLE);
	    } else {
		// otherwise, sleep with BOD disabled to save power
		set_sleep_mode(SLEEP_MODE_PWR_SAVE);
		sleep_bod_disable();
	    }

	    // enter sleep mode
	    sei();
	    sleep_cpu();
	    cli();

	    // analog comparator will have already been enabled
	    // in the TIMER2_COMPB_vect interrupt (icetube.c)
	} while(system_power() == SYSTEM_BATTERY);

	// debounce power-restored signal; delay is actually 100 ms
	_delay_ms(25);  // because system clock is divided by four
    } while(system_power() == SYSTEM_BATTERY);

    wdt_enable(WDTO_8S);
    wdt_reset();

    // enable analog comparator interrupt
    ACSR = _BV(ACBG) | _BV(ACIE) | _BV(ACI);

    system.status &= ~SYSTEM_SLEEP; // clear sleep flag
}


// checks the analog comparator and returns current power source
uint8_t system_power(void) {
    if(ACSR & _BV(ACO)) {
	return SYSTEM_BATTERY;
    } else {
	return SYSTEM_ADAPTOR;
    }
}

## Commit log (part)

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2012-11-05 First commit of icetube project
    Everything seems to work, but features are minimal.
2012-11-07 Improved alarm, date, and time displays
    Before setting the time, the clock prompts for a selection between
    "24-hour" and "12-hour". Before setting the date, the clock prompts
    for a selection between "dd-mm-yy" (EU format) and "mm-dd-yy"
    (US format).
    While the clock is displaying the time, the user may see the current
    day of week, month, and day of month by pressing the set or plus
2012-11-10 Enhanced alarm features
    Snooze is now adjustable and volume can slowly increase while the
    alarm sounds.
    After a system reset, the clock now shows the reason for the reset
    until time is set.
2012-11-16 Sleep bug workaround
    If the system is powered-on using the battery, sleep never woke. This
    seems to be a hardware problem with my atmega128v, but inserting a
    100ms delay before sleep seems to fix the problem.
2012-12-01 Alarm can play music!
    The music and buzzer control code is now in pizo.{c,h} and not in
    alarm.{c,h}. Only one song is implemented---"We Wish You a Merry
    Christmas"---but more may follow.
    Two sleep bugs have also been squashed.
2012-12-10 Brightness control improvements
    The per digit brightness control no longer flickers. Before the
    per-digit brightness control would flicker when a user increased
    around 1/2 of the digits to maximum brightness---not a typical usage
    scenario but might happen nonetheless.
    The autodim minimum and maximum values may now range from -5 to
    20---beyond the allowed brightness range of 0 to 10. The actual
2012-12-22 Multiple alarms by days-of-week
    Three alarms are now supported, but more can be added at compile time
    by changing the ALARM_COUNT macro in alarm.h to something more than 3.
    Each alarm may be configured to sound on "all days", "weekdays",
    "weekends", or "custom". The last option allows users to set a custom
    subset of days-of-week for the particular alarm. Naturally, each
    alarm may be enabled or disabled through the menu, so one need not set
2012-12-27 Animated displays may now be disabled
    The animated displays are enabled by default because they do help
    novices navigate the menus. But some people might find them annoying,
    so they may now be disabled.
2013-01-20 Minor cosmetic changes
    Display transitions in Adafruit compatibility mode are more intuitive,
    and the scroll-left transition runs a bit faster.
2013-02-08 Alternative date formats
    A user may now choose among a variety of date display options under
    "cfg regn"/"date fmt".
2013-02-18 Subsecond time-setting accuracy
    When a user sets the time, the fractional seconds are reset to zero.
    For example, setting the clock to "16 30 00" now sets the clock to
    16:30:00.00. This change is meant to make it possible to manually
    synchronize the Ice Tube Clock with an accurate time source with
    subsecond accuracy.
    Although this seems like a trivial modification, tracking fractional
2013-02-22 Finer control of per-digit brightness
    The per-digit brightness controls ("cfg disp"/ "digt bri"), now
    provide much finer control. With the finer control, the experimental
    brightness gradient correction is not necessary and has been removed.
    The "date fmt" and "time fmt" entries are now in reverse order to
    match the order of "set time" and "set date". This also puts
    "time fmt" next the other time controls, "set dst " and "set zone".
2013-02-23 Display pulse bugfix
    If the firmware was compiled without automatic dimmer support, the
    display-pulsation-on-alarm (if enabled) would fail to restore the
    display to its normal brightness. This has been fixed.
2013-03-13 Minor bugfixes; Dragon compatibility; updated docs
    An alarm volume of 10 saved to EEPROM would be restored as a volume
    of 0! This only happened after a microcontroller reset which only
    happens if the clock battery is absent or dead. This has been fixed.
    The controls in config.h to compensate for phosphor loss in an aging
    VFD tube did not work at all! This has been fixed.
    The Makefile has been modified to allow compatibility with the
2013-03-26 Documentation updates
    The README now contains a troubleshooting section, and the CREDITS
    file contains a reference to my Adafruit Clocks forum post on
    compiling the older firmware projects listed there. The LICENSE file
    has been edited for clarity, but the license remains unchanged.
2013-06-03 Minimized power consumption during sleep
    Power consumption reduced to 10.6 uA at 3.3v without any hardware
    modification. The resistor divider consumes 8.9 uA which means that
    the other components are consuming only 1.7 uA! That is the same as
    in the extended battery hack!
2013-07-18 Documentation updates
    This commit includes minor documentation updates.
2013-07-28 BOD threshold now 1.8v with external clock option
    The BOD threshold has been lowered from 2.7v to 1.8v when using the
    external clock option in config.h.
    This change prevents BOD from resetting the clock prematurely when the
    external clock might have still been able to keep time. Even so, the
    new setting will also allow time loss during sleep when the battery
    gets low. But if users notice time loss after a power outage, they
2013-08-02 Alarm during sleep and non-beep alarm bugfix
    This firmware allows the alarm to sound, even while on battery power.
    But if the alarm sound was set to the three-beep pulse or one of the
    musical alarms, the alarms would not sound when external power was
    lost. This has been fixed.
2013-08-07 Added ability to hard-code special birthday alarm
    Because I am planning to give a couple fully-assembled Ice Tube Clocks
    as gifts, one can now hard code a recipient's birthday in config.h.
    On the hard-coded birthday, the alarm sound will be "For He's a Jolly
    Good Fellow," regardless of what has been configured as the alarm
    sound through the menus (via "cfg alar"/"a. sound").
2013-10-05 Settings-save bugfix (minor)
    The per-digit brightness settings were not being saved to EEPROM, so
    if the clock undergoes a hard reset (no external or battery power),
    the per-digit brightness settings would be reset to the defaults.
    This has now been fixed.
2013-10-05 Revised the xmas-icetube board
    This commit updates the Ice Tube Clock board to revision C. Although
    revision C is untested, the circuit is identical to revision B, so I
    cannot imagine that there would be any problems.
2013-10-25 Added new time display formats
    This commit adds support for four new time display formats, making a
    total of nine. The new formats are rolling colons ("HH:MM:SS"),
    fractions of a second ("HH.MM.SS.FF"), or with single letter
    indicators for AM and PM ("HH.MM.SS.P " or "HH MM A ").
    The rolling colon display based on Russell Walker's rolling colons:
    http://forums.adafruit.com/viewtopic.php?f=41&t=44545
2013-10-31 Time display upon waking bugfix (minor)
    After the clock woke from sleep, time might be incorrectly displayed
    for up to one second. Upon the next tick of the clock, the display
    would be updated. This has been fixed.
2013-11-03 Added license information to hardware READMEs
    I finally found the Ice Tube Clock license information on the Adafruit
    Ice Tube Clock pages, and have included that in the appropriate
    READMEs.
2013-11-09 Minor documentation updates
    This commit includes multiple minor documentation updates.
2013-11-20 New low battery warning
    After ten minutes the system voltage has fallen to whatever is being
    supplied by the battery. At that time, the microcontroller checks the
    system voltage. If the system voltage has fallen below a prespecified
    threshold (config.h), the clock will display a low battery warning
    message upon waking ("bad batt").
2013-11-24 Improved initial default settings
    The default time format, date format, timezone offset, and DST
    settings now default to the computer on which you compile this
    firmware. Also automatic dimming is enabled by default, if that when
    that feature is available. Display pulsing during alarm and snooze is
    now also enabled by default.
    This commit also fixes a bug which caused the automatic fall DST
2013-12-01 Minor hardware documentation updates
    The construction tips section in hardware/README has been edited and
    expanded slightly.
2013-12-11 Optionally flash dots-separators in time formats
    The time display styles with dot-separators may be configured through
    the menus to blink slowly, blink quickly, or not blink. The previous
    behavior was for all dot separators to not blink.
2014-01-07 Updated documentation, changed defaults
    The USAGE describes more details in setting the time, date, and
    miscellaneous format options in the configuration menus.
    The README file now describes how to use the new "verify" targets in
    the Makefile.
    The option under "cfg regn"/"cfg dst" for Western European Time is now
    called "WET" instead of "GMT", because strictly speaking, GMT does not
2014-02-18 New rolling colon separators
    Two new rolling colon separators have been added: a falling bar and
    a blinking colon (blinking top and bottom segments).
2014-03-20 Minor DST bug and possible sleep bug fixed
    Automatic DST state changes now get saved to EEPROM, so they are
    correctly restored after the clock resets. (The clock should only
    reset when the power goes out and the backup battery is dead.) Since
    people expect that time might be wrong when the clock resets, this
    bug was never really problematic.
    Also, I noticed that interrupts are enabled during the piezo_sleep()
2014-04-03 Minor time format bugfix
    When setting the time format under the "cfg regn"/"time fmt" menu, all
    settings should revert back to their previous values if the user
    presses the "menu" button to exit the menu. But the colon style would
    remain changed if the user exited the "dst show/hide" menu or
    "gps show/hide" menu. This has been fixed.
2014-05-06 Improved software temperature compensation during sleep
    This commit only affects clocks with software temperature compensation
    enabled, which requires the addition of a DS18B20 temperature sensor.
    The temperature sensor requires three volts, but system voltage can
    fall below that during sleep. Thus, software temperature compensation
    cannot be accurately performed during sleep.
    After waking from sleep, the clock will measure temperature and
2014-06-18 Changed default boost/brightness range in config.h
    When controlling brightness by adjusting the boost duty cycle, the
    duty cycle may now be adjusted between 8% and 51% through the
    configuration menus. For reference, the Adafruit firmware allows the
    duty cycle to be adjusted from 12% to 40% through the menus.
2014-09-07 Added tpw_rules to CREDITS
2014-11-30 Documentation updates
    The main README and firmware documentation have undergone minor
    revision. Some additional information has been added, but mostly
    only typos have been corrected.
2015-02-28 Added Formulor as an alternative source for parts (thanks Tobias!)
    Tobias Scharmann suggested an alternative source for the custom cut
    case of the xmas-icetube hardware revision; this is now mentioned in
    the hardware/README file.
2015-08-23 Updated hardware/config.h
    The hardware/config.h file contains the default firmware compile-time
    settings for the xmas hardware revision. This file now contains the
    new macro for enabling or disabling the "gps lost" error message.
2019-07-20 Updated code for avr-gcc (9.1.0, 2019)
    The xmas code is now compatible with avr-gcc 9.1.0. (I am using
    Windows x64 binaries from http://blog.zakkemble.net/avr-gcc-builds/ .)
    Three changes were required to support this kit:
    (1) All inline functions are now declared as static to comply with
    better enforcement of the C99 standard.
    (2) Compiler optimization was interfering with the timed register

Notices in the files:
hardware/README:
ShareAlike 3.0 (CC BY-SA 3.0), available from Creative Commons:
http://creativecommons.org/licenses/by-sa/3.0
